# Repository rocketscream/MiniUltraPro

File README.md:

# Mini Ultra Pro
Mini Ultra Pro is an Arduino Compatible 32-bit ARM Cortex M0+ board that is suitable for ultra low power applications. During deep sleep mode, the board consumes only 16.5 uA (with the on-board serial flash chip and radio module in sleep mode). The board comes equipped with a 2Mbyte of serial flash and E19-900M20S2 LoRa radio module. Suitable application includes ultra low power wireless sensor network nodes that runs on Li-Ion/Pol batteries. On-board charger supports Li-Ion/Pol with proper load sharing capability to prolong the lifespan of the battery. The LoRa capable E19-900M20S2 radio module is able to achieve up to 8 km (in semi urban area, frequency of 915 MHz, transmission power of 20 dBm, LoRa spreading factor (SF) of 12, and coding rate (CR) of 4/5). A unique 64-bit MAC ID chip (Microchip's 24AA025E64) is available on-board to be used as DEVEUI in a LoRaWAN network.

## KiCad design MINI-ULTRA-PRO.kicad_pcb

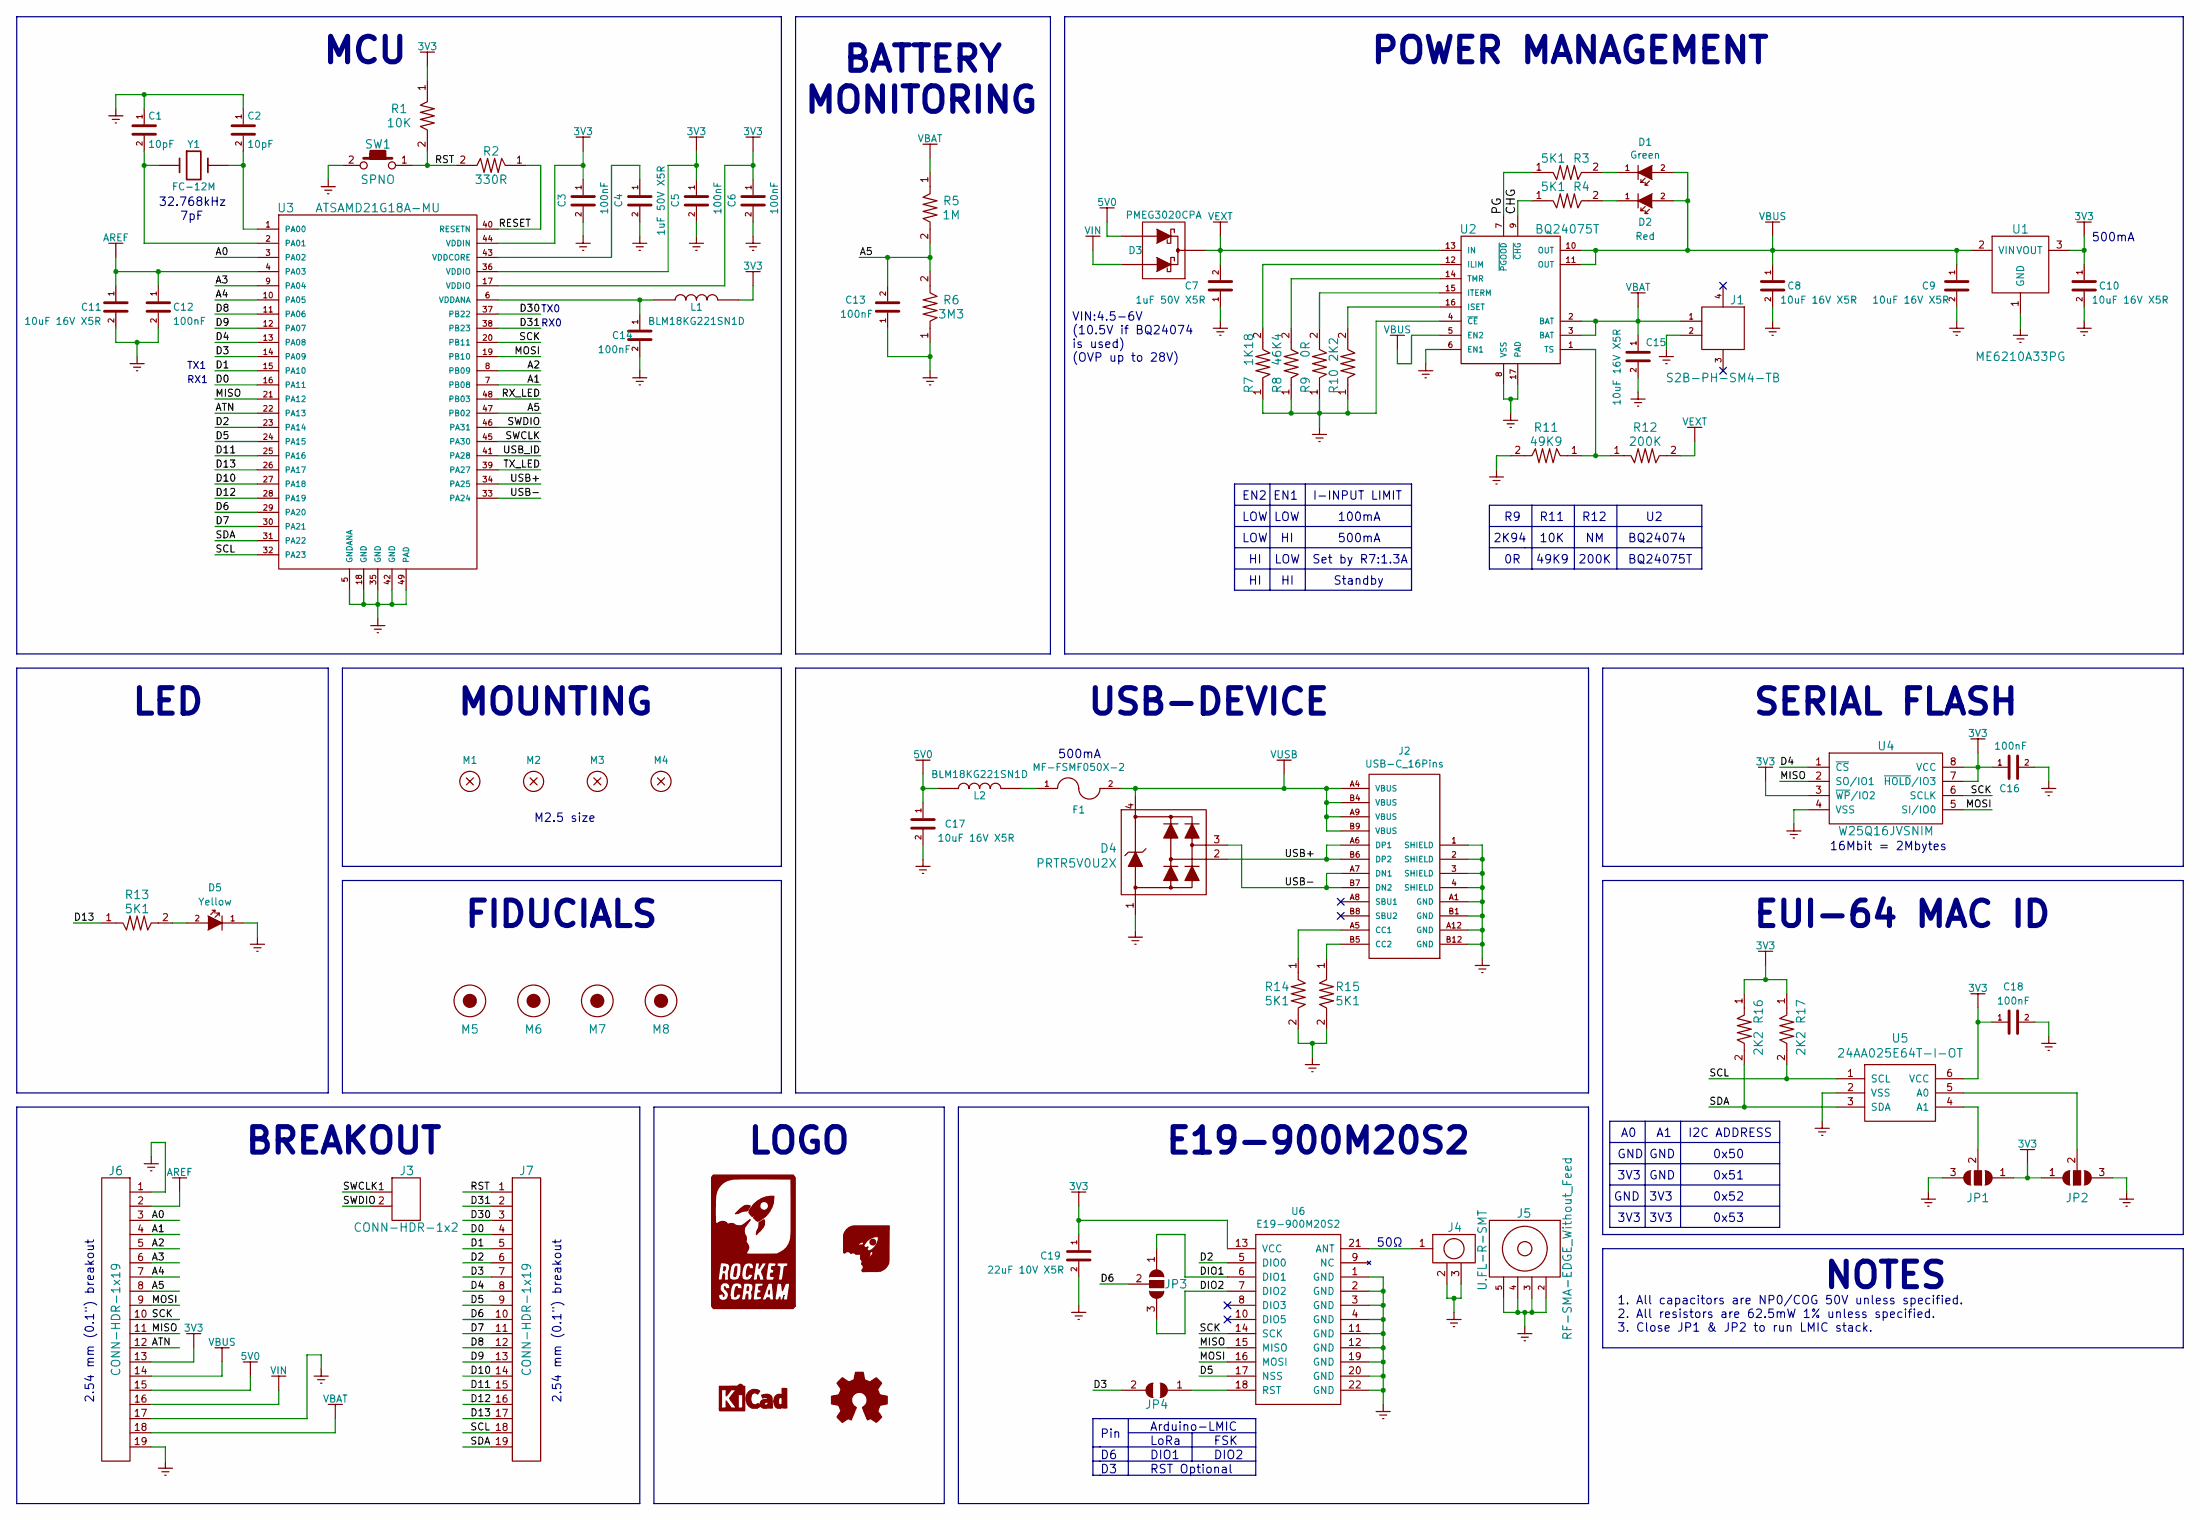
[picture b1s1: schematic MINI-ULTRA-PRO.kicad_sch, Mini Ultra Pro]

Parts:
C1, C2: 10pF; C_0603
C3, C5, C6, C12, C13, C14, C16, C18: 100nF; C_0603
C4, C7: 1uF 50V X5R; C_0603
C8, C9, C10, C11, C15, C17: 10uF 16V X5R; C_0603
C19: 22uF 10V X5R; C_0603
D1: Green; LED_0603
D2: Red; LED_0603
D3: PMEG3020CPA; SOT-1016
D4: PRTR5V0U2X; SOT-143B
D5: Yellow; LED_0603
F1: MF-FSMF050X-2; MF-FSMF
J1: S2B-PH-SM4-TB
J2: USB-C_16Pins; USB-TYPE-C-16PIN-SMD
J3: CONN-HDR-1x2; HDR_1x2_Pitch2.54mm_WithoutSilk
J4: U.FL-R-SMT; U.FL-R-SMT_Extended
J5: RF-SMA-EDGE_Without_Feed
J6, J7: CONN-HDR-1x19; HDR_1x19_Pitch2.54mm_WithoutSilk
JP1, JP2, JP3: JUMPER-2-WAY; JUMPER-2-WAY-SMD
JP4: JUMPER-1-WAY; JUMPER-1-WAY-SMD
L1, L2: BLM18KG221SN1D; I_0603
LOGO1: LOGO-ROCKET-SCREAM; LOGO-ROCKET-SCREAM_Vertical_Small
LOGO2: LOGO-ROCKET-SCREAM; LOGO-ROCKET-SCREAM_Without_Text_XXXSmall
LOGO3: LOGO-KICAD; LOGO-KICAD_XSmall
LOGO4: LOGO-OSHW; LOGO-OSHW_Small
M1, M2, M3, M4: MOUNT_HOLE; HOLE_NPTH_2.2MM
M5, M6, M7, M8: FIDUCIAL; FIDUCIAL-0.5MM_SQUARE
R1: 10K; R_0603
R2: 330R; R_0603
R3, R4, R13, R14, R15: 5K1; R_0603
R5: 1M; R_0603
R6: 3M3; R_0603
R7: 1K18; R_0603
R8: 46K4; R_0603
R9: 0R; R_0603
R10, R16, R17: 2K2; R_0603
R11: 49K9; R_0603
R12: 200K; R_0603
SW1: SPNO; TS-1086E-12
U1: ME6210A33PG; SOT-89_Microchip
U2: BQ24075T; QFN-16_3x3mm_TI
U3: ATSAMD21G18A-MU; QFN-48-1EP_7x7mm_Pitch0.5mm
U4: W25Q16JVSNIM; SOIC-8-N_8S1
U5: 24AA025E64T-I-OT; SOT-23-6
U6: E19-900M20S2
Y1: FC-12M; SC-20S

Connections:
3V3: C3.1, C5.1, C6.1, C10.1, C16.1, C18.1, C19.1, J6.13, JP1.1, JP2.1, L1.2, R1.1, R16.1, R17.1, U1.3 (VOUT), U3.17 (VDDIO), U3.36 (VDDIO), U3.44 (VDDIN), U4.3 (~WP/IO2), U4.7 (~HOLD/IO3), U4.8 (VCC), U5.6 (VCC), U6.13 (VCC)
5V0: C17.1, D3.1 (A), J6.15, L2.1
/A0: J6.3, U3.3 (PA02)
/A1: J6.4, U3.7 (PB08)
/A2: J6.5, U3.8 (PB09)
/A3: J6.6, U3.9 (PA04)
/A4: J6.7, U3.10 (PA05)
/A5: C13.2, J6.8, R5.2, R6.2, U3.47 (PB02)
/ATN: J6.12, U3.22 (PA13)
/CHG: R4.1, U2.9 (~CHG)
/D0: J7.4, U3.16 (PA11)
/D1: J7.5, U3.15 (PA10)
/D2: J7.6, U3.23 (PA14), U6.5 (DIO0)
/D3: J7.7, JP4.2, U3.14 (PA09)
/D4: J7.8, U3.13 (PA08), U4.1 (~CS)
/D5: J7.9, U3.24 (PA15), U6.17 (NSS)
/D6: J7.10, JP3.2, U3.29 (PA20)
/D7: J7.11, U3.30 (PA21)
/D8: J7.12, U3.11 (PA06)
/D9: J7.13, U3.12 (PA07)
/D10: J7.14, U3.27 (PA18)
/D11: J7.15, U3.25 (PA16)
/D12: J7.16, U3.28 (PA19)
/D13: J7.17, R13.1, U3.26 (PA17)
/D30: J7.3, U3.37 (PB22)
/D31: J7.2, U3.38 (PB23)
/DIO1: JP3.1, U6.6 (DIO1)
/DIO2: JP3.3, U6.7 (DIO2)
/MISO: J6.11, U3.21 (PA12), U4.2 (SO/IO1), U6.15 (MISO)
/MOSI: J6.9, U3.19 (PB10), U4.5 (SI/IO0), U6.16 (MOSI)
/PG: R3.1, U2.7 (~PGOOD)
/RESET: R2.1, U3.40 (RESETN)
/RST: J7.1, R1.2, R2.2, SW1.1
/RX_LED: U3.48 (PB03)
/SCK: J6.10, U3.20 (PB11), U4.6 (SCLK), U6.14 (SCK)
/SCL: J7.18, R17.2, U3.32 (PA23), U5.1 (SCL)
/SDA: J7.19, R16.2, U3.31 (PA22), U5.3 (SDA)
/SWCLK: J3.1, U3.45 (PA30)
/SWDIO: J3.2, U3.46 (PA31)
/TX_LED: U3.39 (PA27)
/USB+: D4.2, J2.A6 (DP1), J2.B6 (DP2), U3.34 (PA25)
/USB-: D4.3, J2.A7 (DN1), J2.B7 (DN2), U3.33 (PA24)
/USB_ID: U3.41 (PA28)
AREF: C11.1, C12.1, J6.2, U3.4 (PA03)
GND: C1.1, C2.1, C3.2, C4.2, C5.2, C6.2, C7.1, C8.2, C9.2, C10.2, C11.2, C12.2, C13.1, C14.2, C15.2, C16.2, C17.2, C18.2, C19.2, D4.1, D5.1 (K), J1.2, J2.1 (SHIELD), J2.2 (SHIELD), J2.3 (SHIELD), J2.4 (SHIELD), J2.A1 (GND), J2.A12 (GND), J2.B1 (GND), J2.B12 (GND), J4.2, J4.3, J5.2, J5.3, J5.4, J5.5, J6.1, J6.17, J6.19, JP1.3, JP2.3, R6.1, R7.1, R8.1, R9.1, R10.1, R11.2, R14.2, R15.2, SW1.2, U1.1 (GND), U2.4 (~CE), U2.6 (EN1), U2.8 (VSS), U2.17 (PAD), U3.5 (GNDANA), U3.18 (GND), U3.35 (GND), U3.42 (GND), U3.49 (PAD), U4.4 (VSS), U5.2 (VSS), U6.1 (GND), U6.2 (GND), U6.3 (GND), U6.4 (GND), U6.11 (GND), U6.12 (GND), U6.19 (GND), U6.20 (GND), U6.22 (GND)
unnamed: C1.2, U3.2 (PA01), Y1.1
unnamed: C2.2, U3.1 (PA00), Y1.2
unnamed: C4.1, U3.43 (VDDCORE)
unnamed: C14.1, L1.1, U3.6 (VDDANA)
unnamed: D1.1 (K), R3.2
unnamed: D2.1 (K), R4.2
unnamed: D5.2 (A), R13.2
unnamed: F1.1, L2.2
unnamed: J2.A5 (CC1), R14.1
unnamed: J2.B5 (CC2), R15.1
unnamed: J4.1, U6.21 (ANT)
unnamed: JP1.2, U5.4 (A1)
unnamed: JP2.2, U5.5 (A0)
unnamed: JP4.1, U6.18 (RST)
unnamed: R7.2, U2.12 (ILIM)
unnamed: R8.2, U2.14 (TMR)
unnamed: R9.2, U2.15 (ITERM)
unnamed: R10.2, U2.16 (ISET)
unnamed: R11.1, R12.1, U2.1 (TS)
VBAT: C15.1, J1.1, J6.18, R5.1, U2.2 (BAT), U2.3 (BAT)
VBUS: C8.1, C9.1, D1.2 (A), D2.2 (A), J6.14, U1.2 (VIN), U2.5 (EN2), U2.10 (OUT), U2.11 (OUT)
VEXT: C7.2, D3.3 (K), R12.2, U2.13 (IN)
VIN: D3.2 (A), J6.16
VUSB: D4.4, F1.2, J2.A4 (VBUS), J2.A9 (VBUS), J2.B4 (VBUS), J2.B9 (VBUS)

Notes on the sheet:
BQ24075T
49K9
FIDUCIALS
I-INPUT LIMIT
M2.5 size
500mA
POWER MANAGEMENT
0x53
R12
BREAKOUT
2.54 mm (0.1") breakout
BQ24074
TX0
MOUNTING
SERIAL FLASH
HI HI
2K94
GND
0x50
100mA
EUI-64 MAC ID
16Mbit = 2Mbytes
MCU
Set by R7:1.3A
LOW HI
Standby
RST Optional
Arduino-LMIC
0x52
HI LOW
LOGO
I2C ADDRESS
200K
E19-900M20S2
7pF
LED
RX0
1. All capacitors are NP0/COG 50V unless specified. 2. All resistors are 62.5mW 1% unless specified. 3. Close JP1 & JP2 to run LMIC stack.
3V3
VIN:4.5-6V (10.5V if BQ24074 is used) (OVP up to 28V)

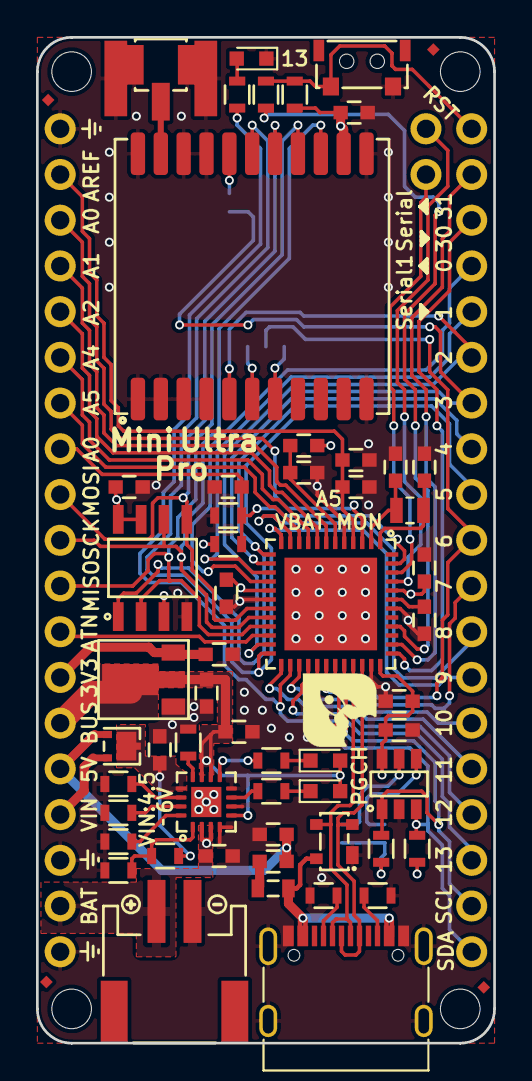
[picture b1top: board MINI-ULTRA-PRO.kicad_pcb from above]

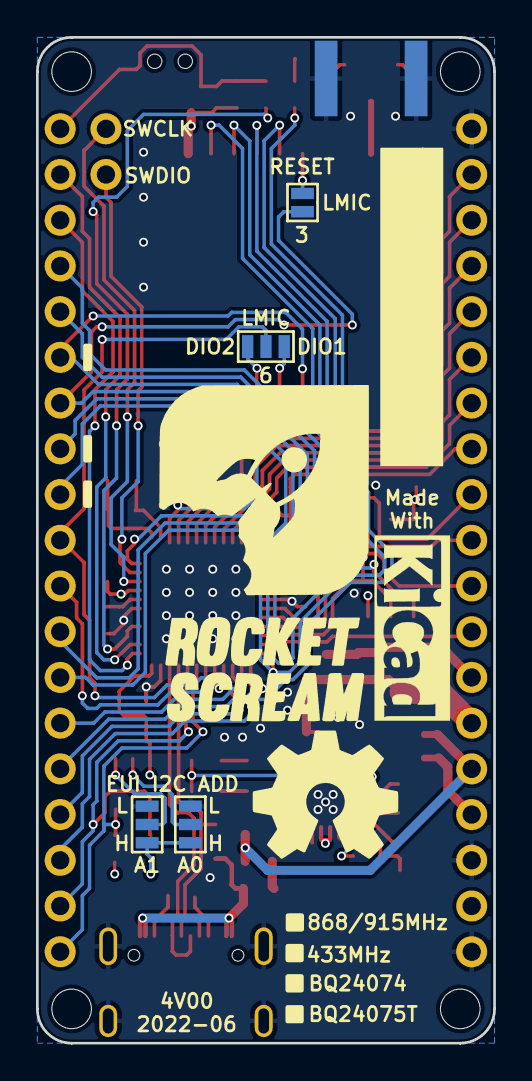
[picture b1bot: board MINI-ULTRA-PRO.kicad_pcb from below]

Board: 4 copper layers, 25.4 x 55.9 mm, 75 parts (8 on the bottom side), 66 nets.

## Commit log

2016-02-22 Revision 0.20
2016-02-22 Initial public release for version 0.20.
2017-07-19 Version 0.40
2017-09-06 Added OTAA TTN example code
2017-09-07 Fix LMIC_UNUSED_PIN on D7 in LoRa mode
2017-09-07 Corrected EUI-64 sequence printing on USB port during power up
2018-02-21 Version 0.50 - V3
2018-09-04 Enclosure
2018-09-04 Revert "Enclosure"
2018-09-04 Remove enclosure files for Mini Ultra LoRaWAN
2022-07-26 Remove KiCad v5 files
2022-07-26 Version 4.00 - V4
2022-07-26 Remove KiCad v5 footprints
